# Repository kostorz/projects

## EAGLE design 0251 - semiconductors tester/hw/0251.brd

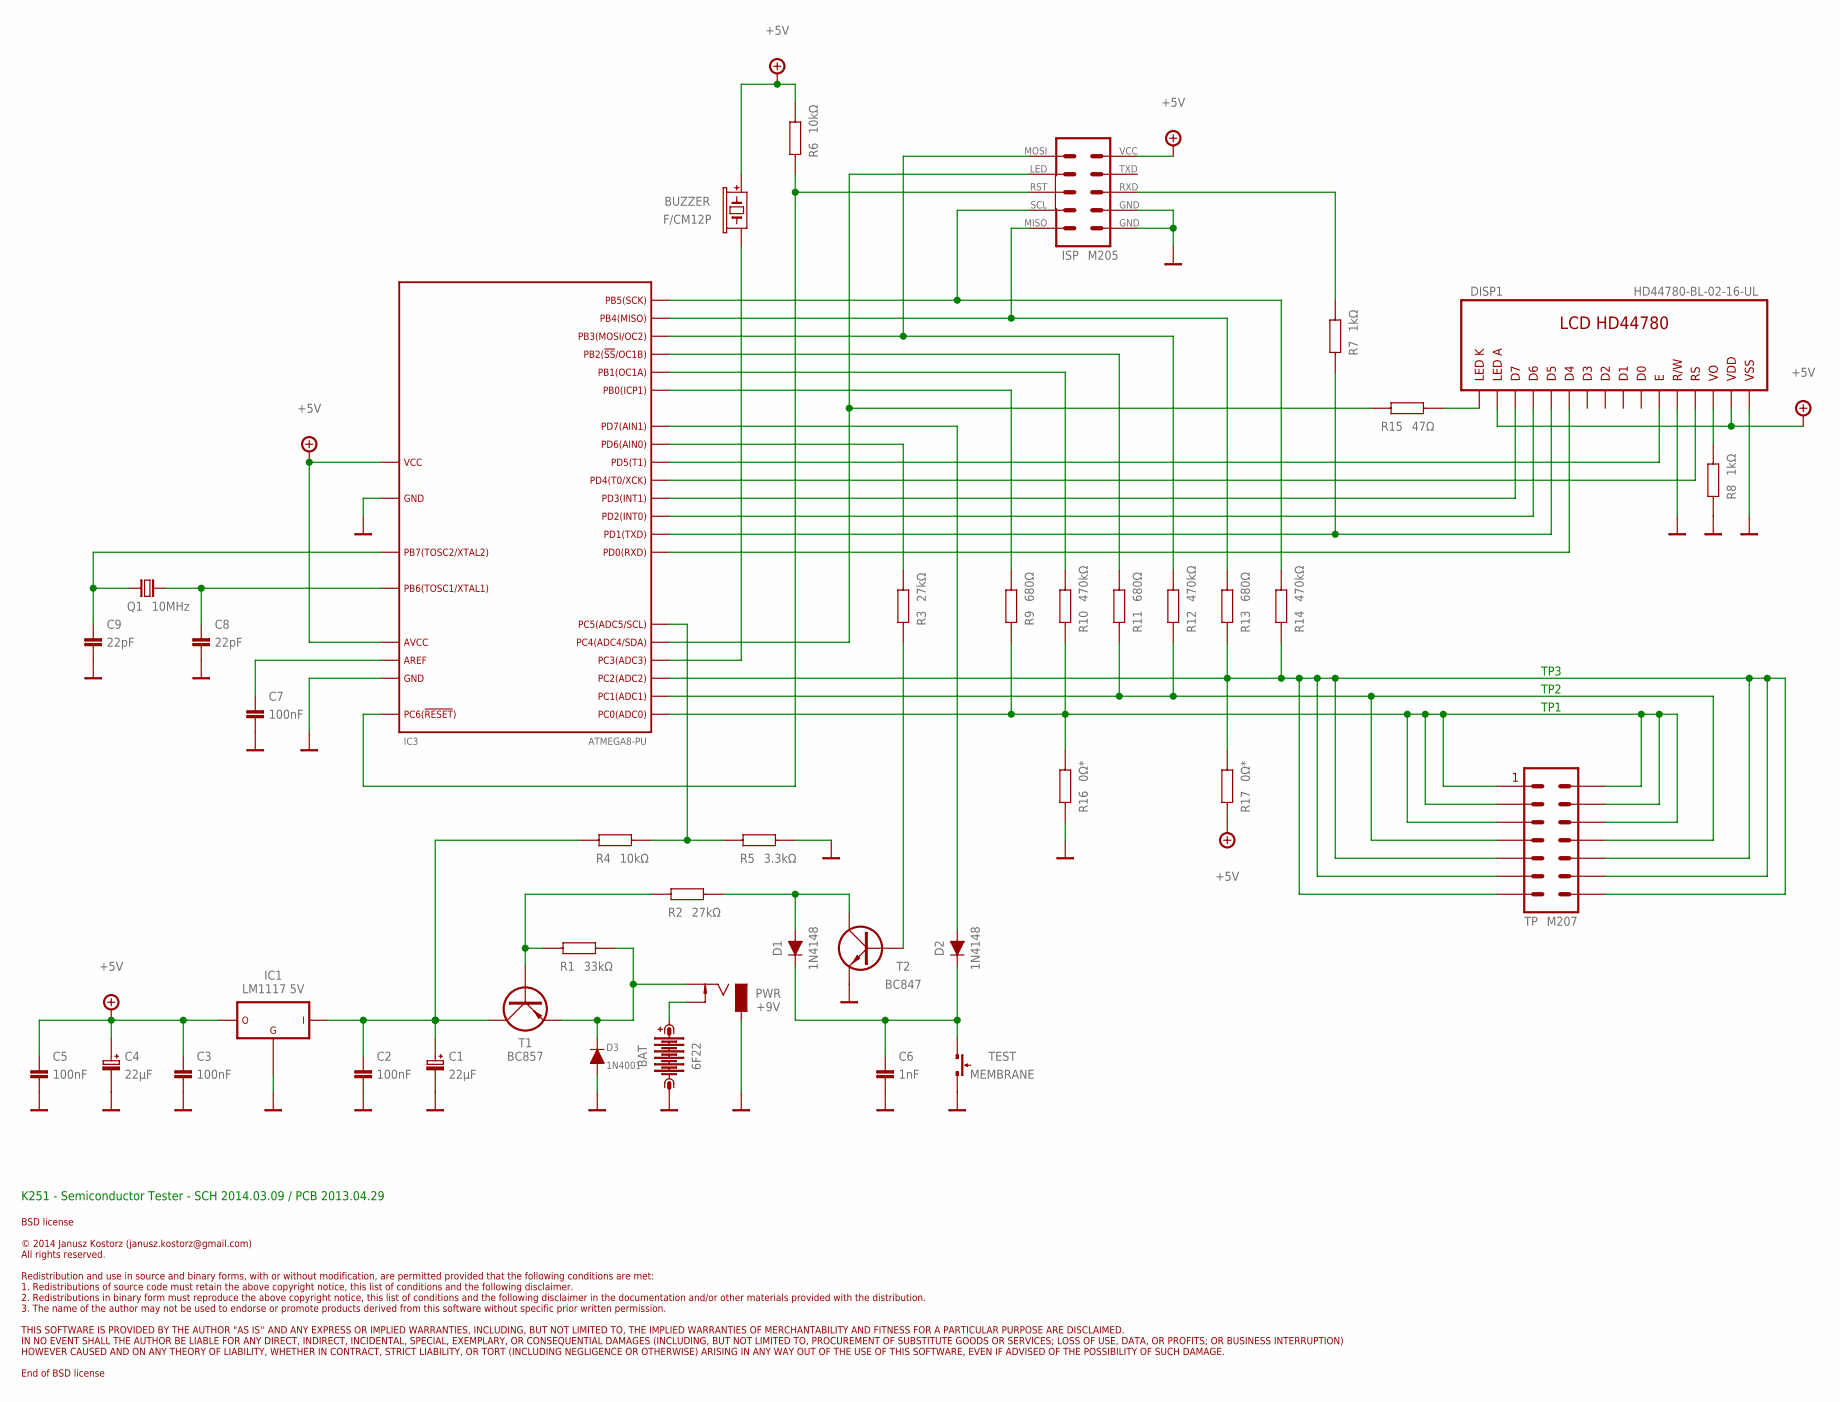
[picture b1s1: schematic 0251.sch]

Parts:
BAT: 6F22; AB9V
BUZZER: F/CM12P; BUZZER_F/CM12P
C1, C4: 22µF; E-050-110-020-05
C2, C3, C5, C7: 100nF; C1206
C6: 1nF; C1206
C8, C9: 22pF; C1206
D1, D2: 1N4148; DO35-10
D3: 1N4001; DO41-10
DISP1: HD44780-BL-02-16-UL; 02-16-UL-BL
IC1: LM1117 5V; TO252
IC3: ATMEGA8-PU; DIP254P800X550-28B
ISP: M205; MM-10-H
PWR: +9V; DCJ0303
Q1: 10MHz; HC49/S
R1: 33kΩ; R1206
R2, R3: 27kΩ; R1206
R4, R6: 10kΩ; R1206
R5: 3.3kΩ; R1206
R7, R8: 1kΩ; R1206
R9, R11, R13: 680Ω; 0207/12
R10, R12, R14: 470kΩ; 0207/12
R15: 47Ω; R1206
R16, R17: 0Ω*; R1206
T1: BC857; SOT23-BEC
T2: BC847; SOT23-BEC
TEST: MEMBRANE; B3F-10XX-M
TP: M207; 2-7

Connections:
+5V: BUZZER.+ (1), C3.2, C4.+, C5.2, DISP1.2 (VDD), DISP1.15 (A), IC1.2 (OUT), IC3.7 (VCC), IC3.20 (AVCC), ISP.P$2 (VCC), R6.2, R17.2
GND: BAT.-, C1.-, C2.1, C3.1, C4.-, C5.1, C6.1, C7.1, C8.1, C9.1, D3.A, DISP1.1 (VSS), DISP1.5 (R/W), IC1.1 (GND), IC3.8 (GND), IC3.22 (GND), ISP.P$8 (GND), ISP.P$10 (GND), PWR.1, R5.1, R8.1, R16.2, T2.E, TEST.1 (S)
unnamed: ISP.P$6 (RXD), R7.1
unnamed: DISP1.16 (K), R15.1
unnamed: D3.C, PWR.3, R1.2, T1.E
unnamed: IC3.12 (PD6), R3.2
unnamed: C1.+, C2.2, IC1.3 (IN), R4.2, T1.C
unnamed: C6.2, D1.C, D2.C, TEST.3
unnamed: BAT.+, PWR.2
unnamed: D1.A, R2.1, T2.C
unnamed: IC3.14 (PB0), R9.1
unnamed: IC3.15 (PB1), R10.1
unnamed: C7.2, IC3.21 (AREF)
unnamed: DISP1.3 (VO), R8.2
unnamed: IC3.16 (PB2), R11.1
unnamed: IC3.17 (PB3), ISP.P$1 (MOSI), R12.1
unnamed: IC3.28 (PC5), R4.1, R5.2
unnamed: IC3.18 (PB4), ISP.P$9 (MISO), R13.1
unnamed: IC3.19 (PB5), ISP.P$7 (SCL), R14.1
unnamed: DISP1.11 (DB4), IC3.2 (PD0)
unnamed: DISP1.12 (DB5), IC3.3 (PD1), R7.2
unnamed: DISP1.13 (DB6), IC3.4 (PD2)
unnamed: DISP1.14 (DB7), IC3.5 (PD3)
unnamed: R1.1, R2.2, T1.B
unnamed: DISP1.4 (RS), IC3.6 (PD4)
unnamed: DISP1.6 (E), IC3.11 (PD5)
unnamed: D2.A, IC3.13 (PD7)
unnamed: IC3.27 (PC4), ISP.P$3 (LED), R15.2
unnamed: BUZZER.- (2), IC3.26 (PC3)
unnamed: IC3.1 (PC6), ISP.P$5 (RST), R6.1
unnamed: C9.2, IC3.10 (PB7), Q1.1
unnamed: C8.2, IC3.9 (PB6), Q1.2
T2: R3.1, T2.B
TP1: IC3.23 (PC0), R9.2, R10.2, R16.1, TP.1, TP.2, TP.3, TP.4, TP.5, TP.6
TP2: IC3.24 (PC1), R11.2, R12.2, TP.7, TP.8
TP3: IC3.25 (PC2), R13.2, R14.2, R17.1, TP.9, TP.10, TP.11, TP.12, TP.13, TP.14

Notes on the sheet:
K251 - Semiconductor Tester - SCH 2014.03.09 / PCB 2013.04.29
TP1
TP2
TP3

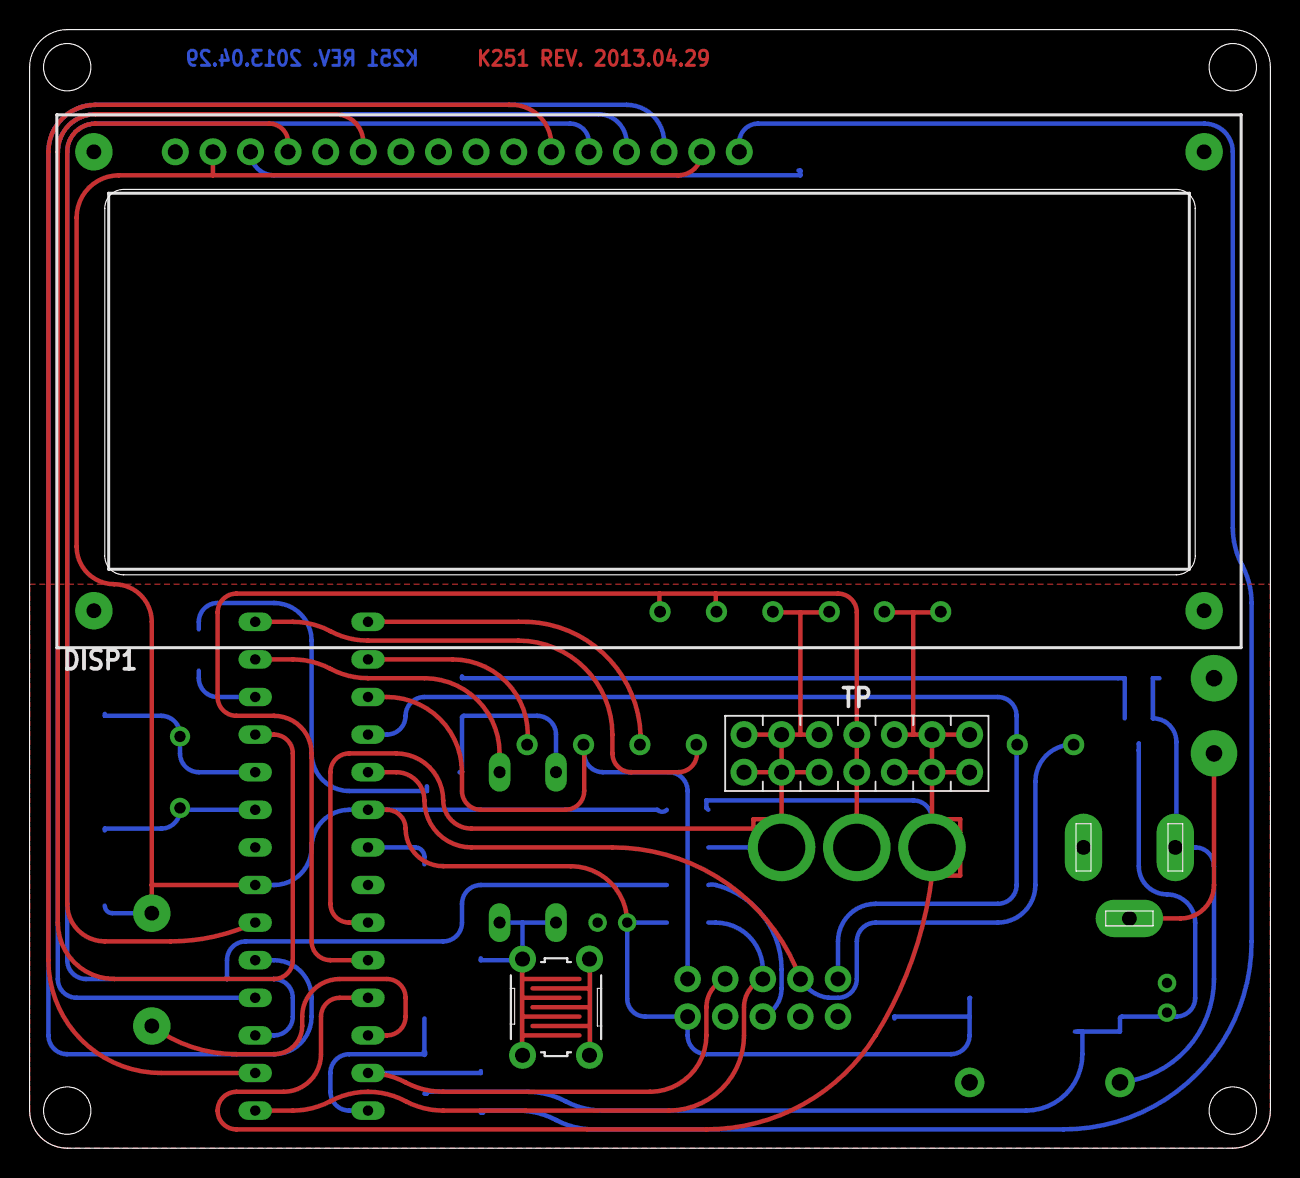
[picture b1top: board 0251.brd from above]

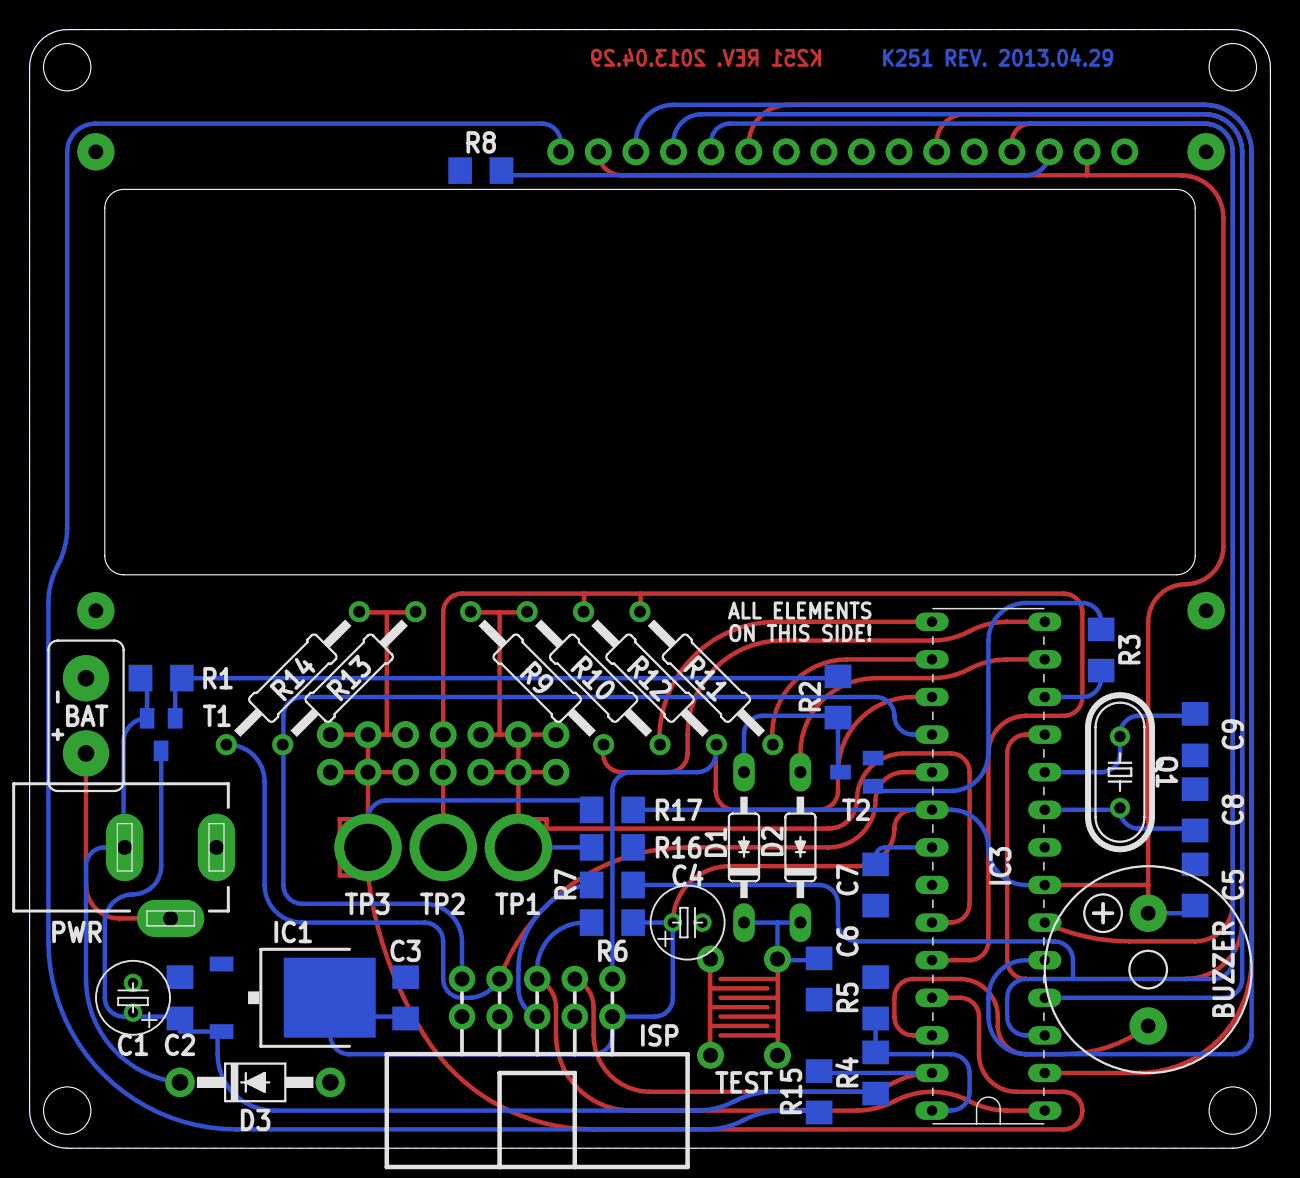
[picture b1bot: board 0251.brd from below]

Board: 2 copper layers, 83.8 x 75.6 mm, 43 parts (40 on the bottom side), 36 nets.

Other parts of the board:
U$1: CE
U$2: ESD

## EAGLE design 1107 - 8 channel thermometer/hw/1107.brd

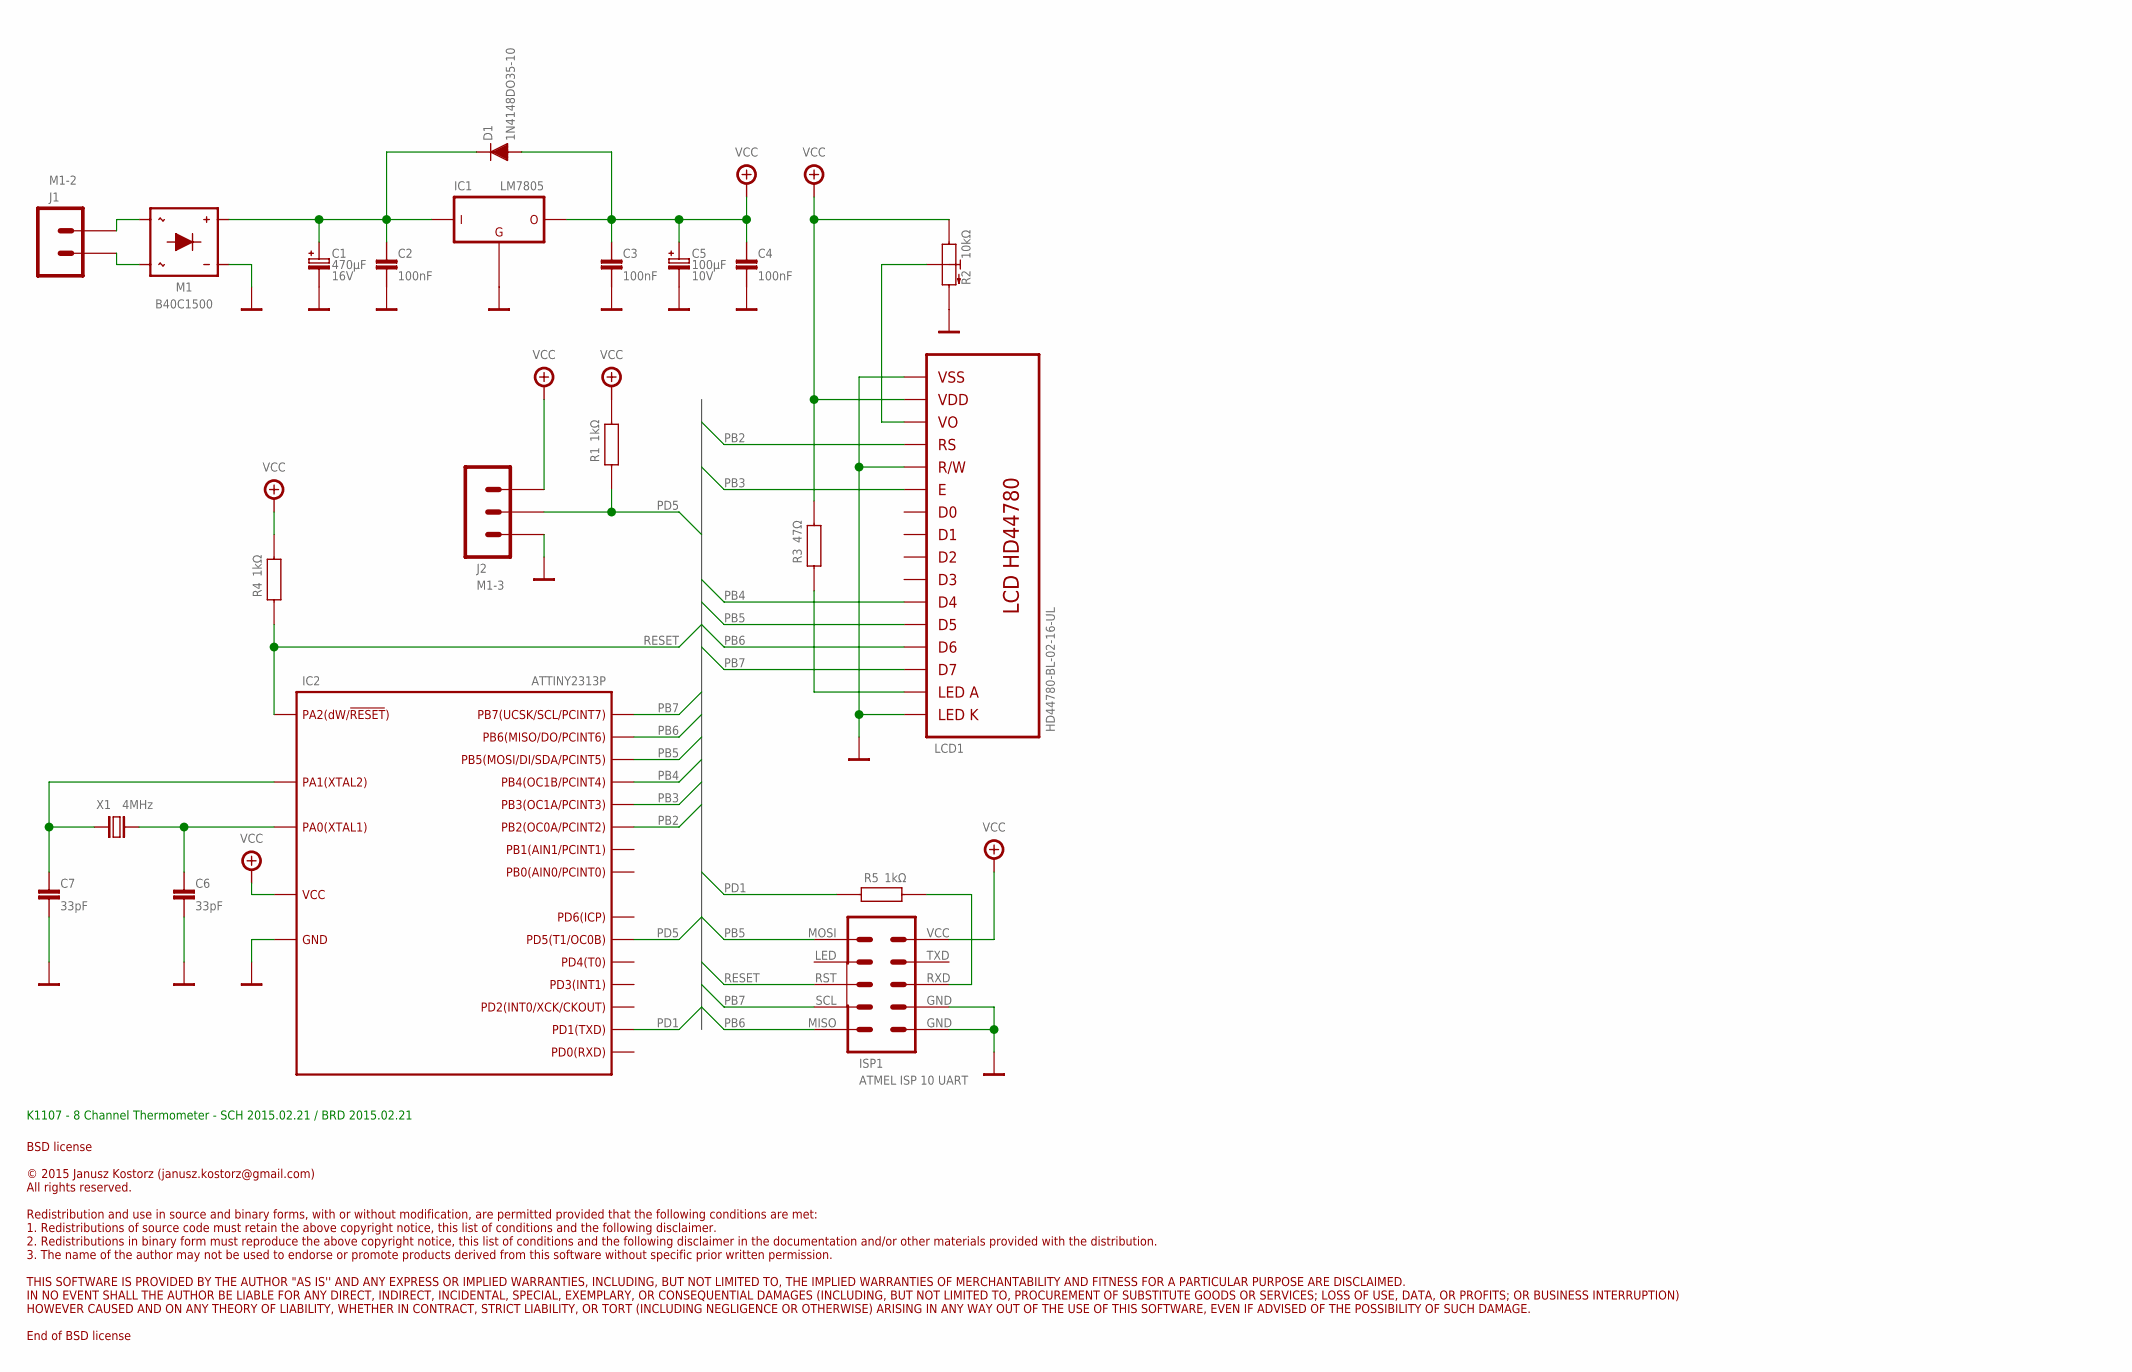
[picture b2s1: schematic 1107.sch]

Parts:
C1: 470µF; E-080-150-035-060
C2, C3, C4: 100nF; C1206
C5: 100µF; E-050-150-020-050
C6, C7: 33pF; C1206
D1: 1N4148DO35-10; DO35-10
IC1: LM7805; TO220-H
IC2: ATTINY2313P; DIL20
ISP1: ATMEL ISP 10 UART; MM-10-V
J1: M1-2; 1-2
J2: M1-3; 1-3
LCD1: HD44780-BL-02-16-UL; 02-16-UL-BL
M1: B40C1500; RB1A
R1, R4, R5: 1kΩ; M1206
R2: 10kΩ; POT_CA6V
R3: 47Ω; M1206
X1: 4MHz; HC49/S

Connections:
A: LCD1.15 (A), R3.1
GND: C1.-, C2.2, C3.2, C4.2, C5.-, C6.2, C7.2, IC1.2 (GND), IC2.10 (GND), ISP1.8 (GND), ISP1.10 (GND), J2.3, LCD1.1 (VSS), LCD1.5 (R/W), LCD1.16 (K), M1.-, R2.E
unnamed: C6.1, IC2.5 (PA0), X1.2
unnamed: J1.1, M1.AC@2
unnamed: C7.1, IC2.4 (PA1), X1.1
unnamed: C1.+, C2.1, D1.C, IC1.1 (IN), M1.+
unnamed: LCD1.3 (VO), R2.S
unnamed: J1.2, M1.AC@1
unnamed: ISP1.6 (RXD), R5.2
PB2: IC2.14 (PB2), LCD1.4 (RS)
PB3: IC2.15 (PB3), LCD1.6 (E)
PB4: IC2.16 (PB4), LCD1.11 (DB4)
PB5: IC2.17 (PB5), ISP1.1 (MOSI), LCD1.12 (DB5)
PB6: IC2.18 (PB6), ISP1.9 (MISO), LCD1.13 (DB6)
PB7: IC2.19 (PB7), ISP1.7 (SCL), LCD1.14 (DB7)
PD1: IC2.3 (PD1), R5.1
PD5: IC2.9 (PD5), J2.2, R1.1
RESET: IC2.1 (PA2), ISP1.5 (RST), R4.1
VCC: C3.1, C4.1, C5.+, D1.A, IC1.3 (OUT), IC2.20 (VCC), ISP1.2 (VCC), J2.1, LCD1.2 (VDD), R1.2, R2.A, R3.2, R4.2

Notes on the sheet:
K1107 - 8 Channel Thermometer - SCH 2015.02.21 / BRD 2015.02.21

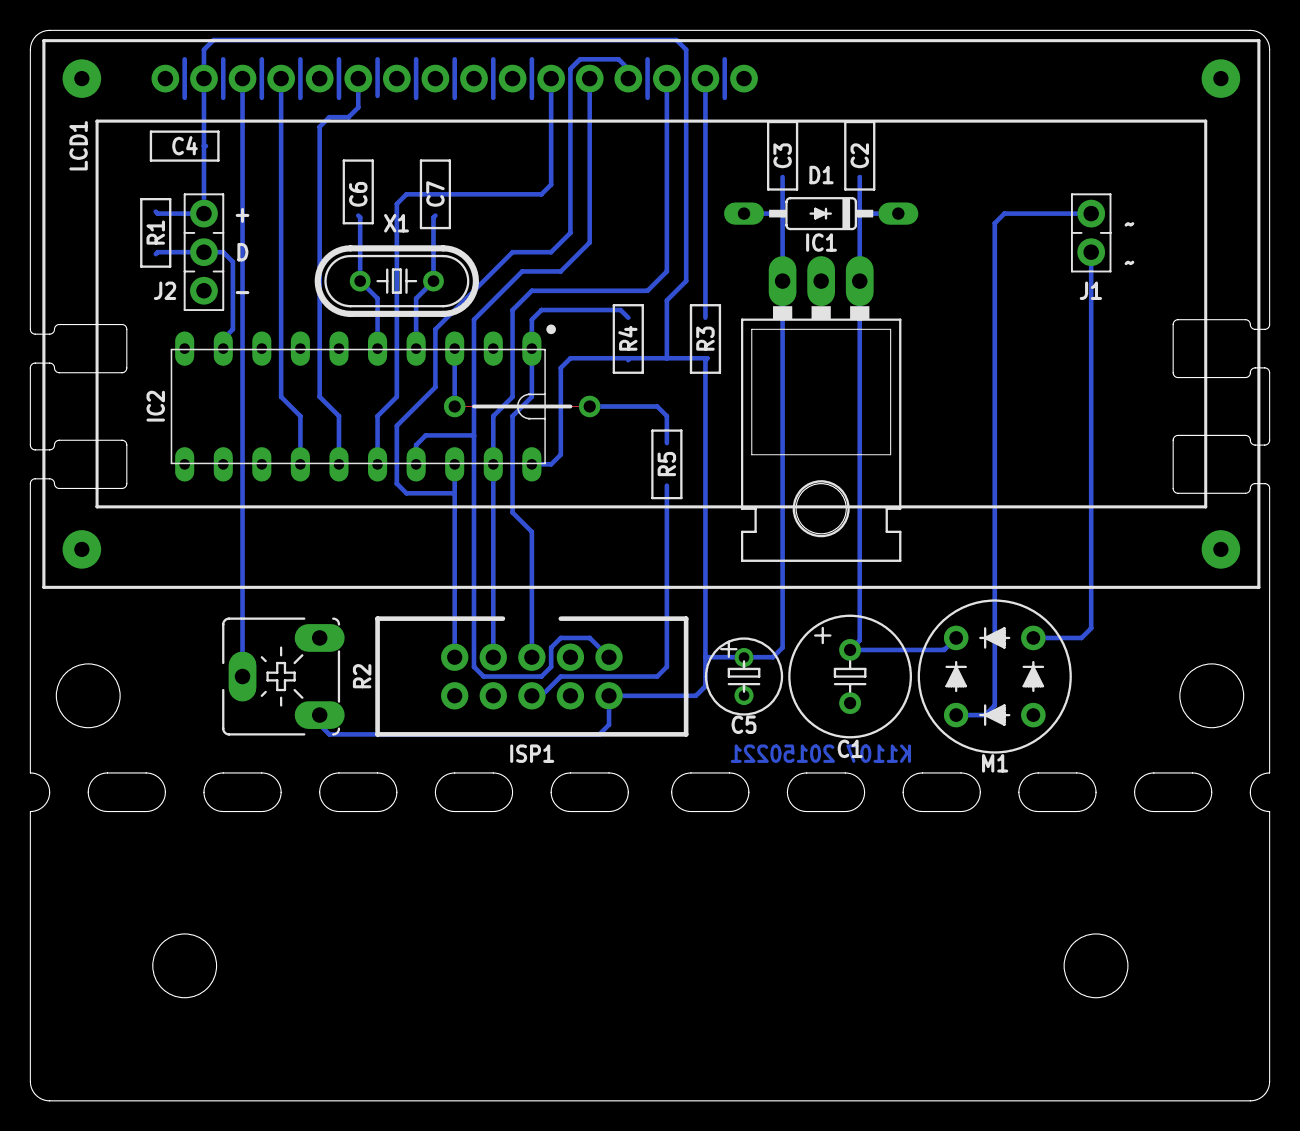
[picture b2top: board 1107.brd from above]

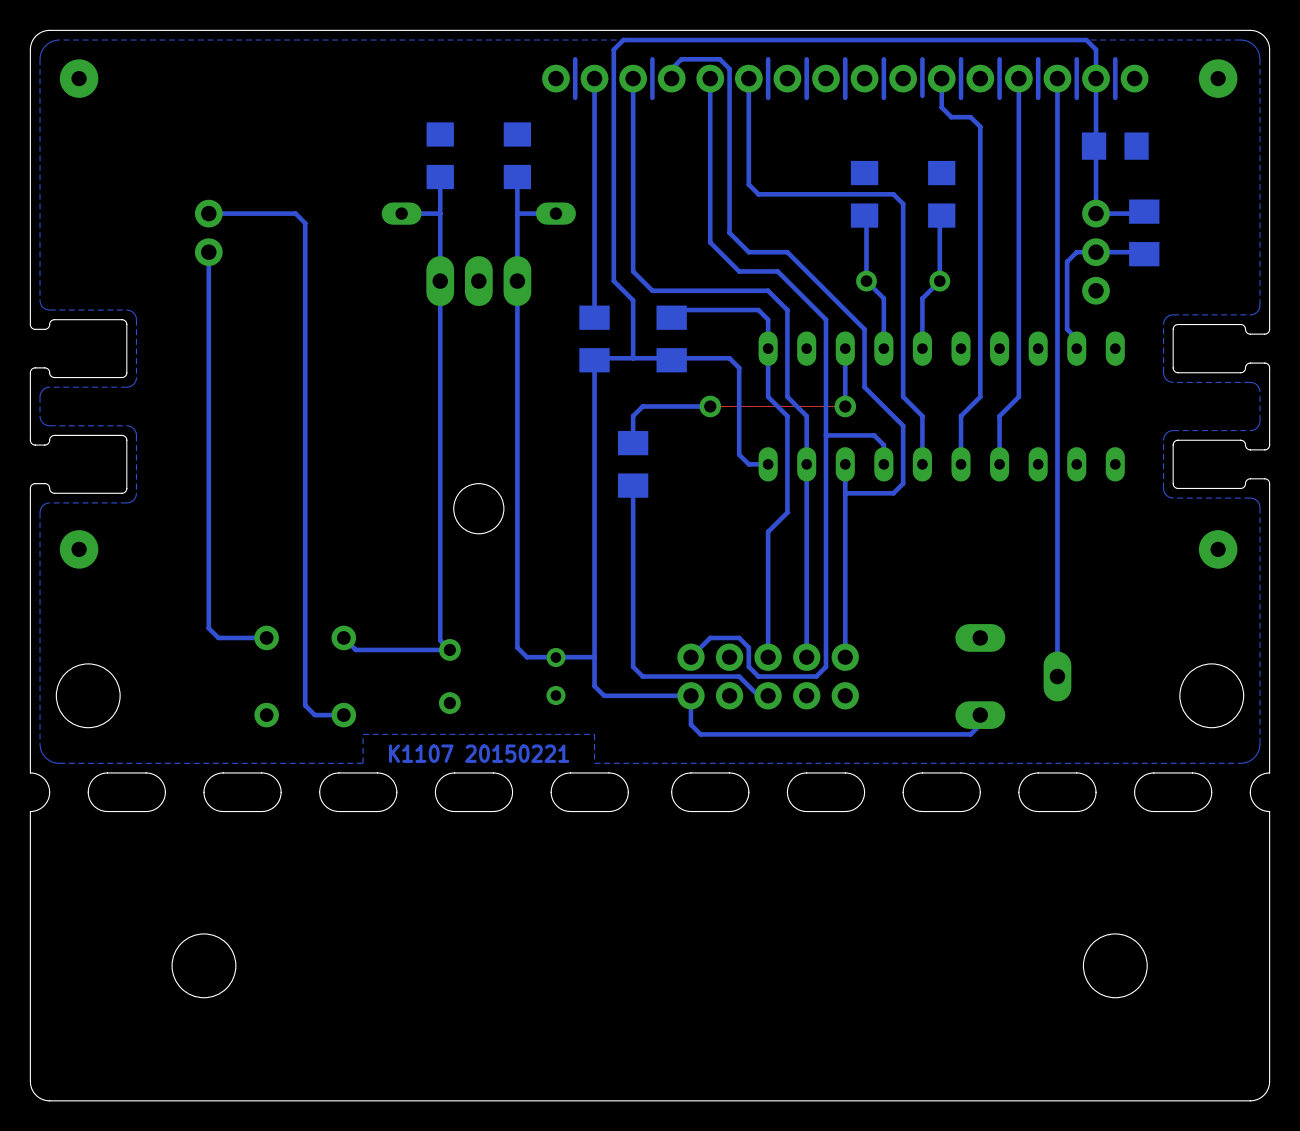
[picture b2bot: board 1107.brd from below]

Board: 2 copper layers, 81.6 x 70.5 mm, 21 parts (9 on the bottom side), 19 nets.

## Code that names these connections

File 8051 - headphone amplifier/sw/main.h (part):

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/*
*
* MANUAL:
* PB0 - output active low	- sterowanie diodą led "power"
* PB1 - input pullup on		- wejście A enkodera
* PB2 - input pullup on		- wejście B enkodera
* PB3 - input pullup on		- kontrola obecności napięcia zasilania dodatniego, 0L oznacza obecność napięcia, 1L oznacza zanik napięcia
* PB4 - input pullup on		- kontrola obecności napięcia zasilania ujemnego, 0L oznacza obecność napięcia, 1L oznacza zanik napięcia
* PB5 - input pullup on		- przycisk funcji dodatkowych, 0L oznacza naciśnięty przycisk
*
* PC0 - output active high	- sterowanie przekaźnikiem zasilania części analogowej
* PC1 - output active high	- sterowanie przekaźnikiem odłączania wyjścia słuchawkowego
* PC2 - output active low	- sterowanie diodą led "mute"
* PC3 - output active low	- sterowanie potencjometrem cyfrowym - sygnał "mute"
* PC4 - input pullup on		- sterowanie potencjometrem cyfrowym - sygnał "data read"
* PC5 - output active low	- sterowanie diodą led "high volume"
*
* PD0 - service			- TXD
* PD1 - service			- RXD
* PD2 - input pullup on		- przycisk zasilania i wyciszania, 0L oznacza naciśnięty przycisk
* PD3 - input pullup off		- sygnał zdalnego sterowania podczerwienią, sygnał obecności słuchawek - 0L oznacza ich brak
* PD4 - output active low	- sterowanie potencjometrem cyfrowym - sygnał "clock"
* PD5 - output active low	- sterowanie potencjometrem cyfrowym - sygnał "data write"
* PD6 - output active low	- sterowanie potencjometrem cyfrowym - sygnał "csl"
* PD7 - output active low	- sterowanie potencjometrem cyfrowym - sygnał "csr"
*
*/

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
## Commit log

2015-08-18 init
2015-08-19 init 8051
2015-08-19 update 8051
2015-08-19 init 1107
2015-08-19 init 0251
2015-08-19 update 1107
2015-08-22 optymalizacja kodu
2015-08-22 poprawiony numer wersji
2015-08-23 poprawiony opis
2015-08-26 init 0157
2015-08-27 add lines
2015-10-11 release

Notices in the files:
8051 - headphone amplifier/sw/main.h:
BSD license
© 2015 Janusz Kostorz (janusz.kostorz@gmail.com)
All rights reserved.
End of BSD license
0251 - semiconductors tester/hw/0251.brd:
BSD licence
© 2013 Janusz Kostorz (janusz.kostorz@gmail.com)
End of BSD licence
parts and their libraries:
con-isp: © 2014 Janusz Kostorz (janusz.kostorz@gmail.com)
licence: - new - BSD licence;
license: - update - update year in BSD licence;
